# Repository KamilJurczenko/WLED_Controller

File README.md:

# WLED_Controller
My first designed pcb board to control some LEDs with a ESP-WROOM-32.

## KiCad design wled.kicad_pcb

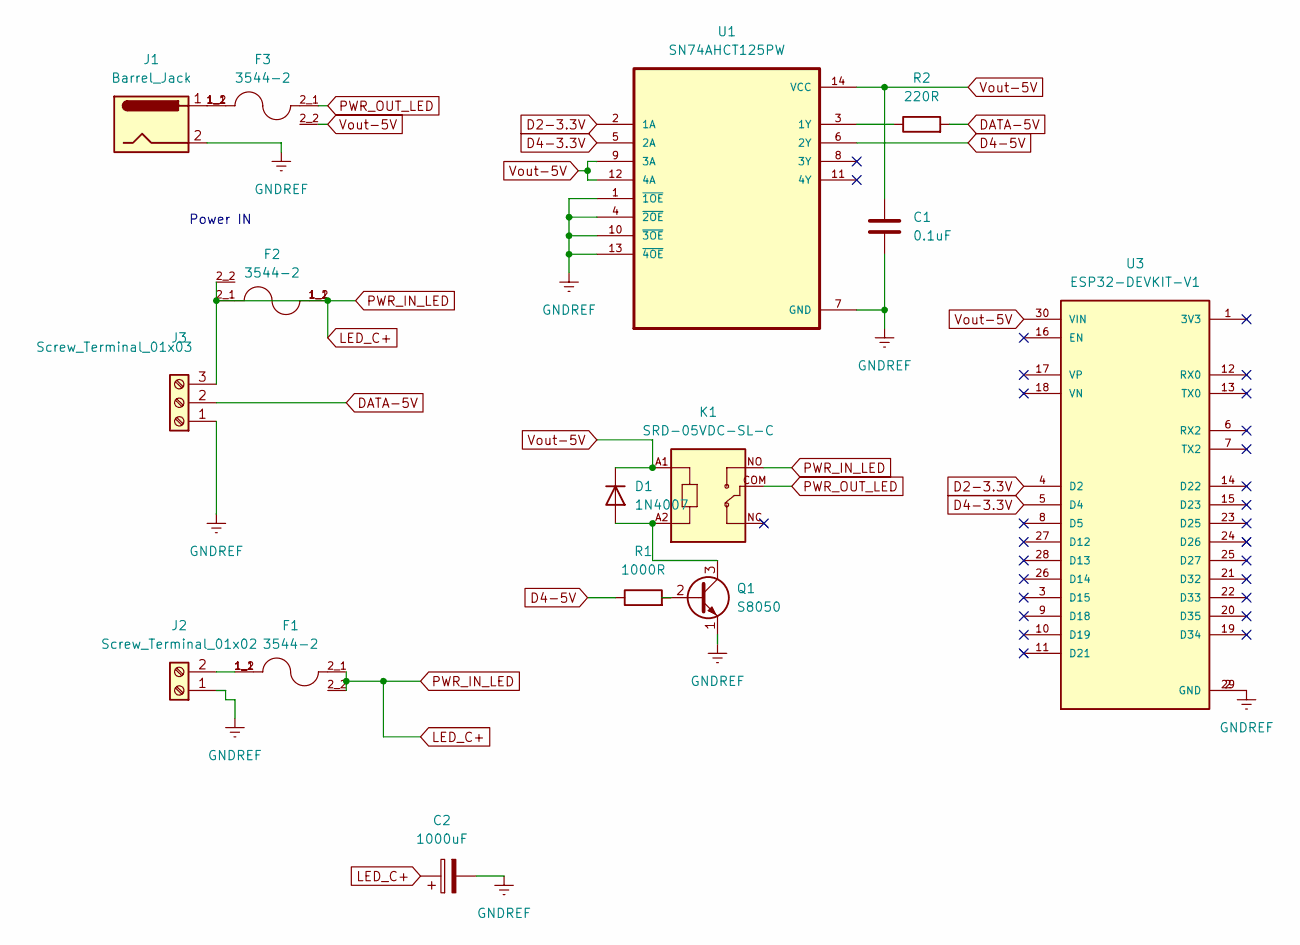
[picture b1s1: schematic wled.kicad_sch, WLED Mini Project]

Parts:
C1: 0.1uF; C_Disc_D5.0mm_W2.5mm_P2.50mm
C2: 1000uF; CP_Radial_D10.0mm_P5.00mm
D1: 1N4007; D_DO-41_SOD81_P10.16mm_Horizontal
F1, F2, F3: 3544-2; FUSE_3544-2; PARTREV C
J1: Barrel_Jack; BarrelJack_Horizontal
J2: Screw_Terminal_01x02; TerminalBlock_Phoenix_MKDS-1,5-2-5.08_1x02_P5.08mm_Horizont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
J3: Screw_Terminal_01x03; TerminalBlock_Phoenix_MKDS-1,5-3_1x03_P5.00mm_Horizontal
K1: SRD-05VDC-SL-C; RELAY_SRD-05VDC-SL-C
Q1: S8050; TO-92_Inline
R1: 1000R; R_Axial_DIN0207_L6.3mm_D2.5mm_P7.62mm_Horizontal
R2: 220R; R_Axial_DIN0207_L6.3mm_D2.5mm_P7.62mm_Horizontal
U1: SN74AHCT125PW; DIP794W45P254L1930H508Q14
U3: ESP32-DEVKIT-V1; MODULE_ESP32_DEVKIT_V1; PARTREV N/A

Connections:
D2-3.3V: U1.2 (1A), U3.4 (D2)
D4-3.3V: U1.5 (2A), U3.5 (D4)
D4-5V: R1.1, U1.6 (2Y)
DATA-5V: J3.2, R2.2
GNDREF: C1.2, C2.2, J1.2, J2.1, J3.1, Q1.1 (E), U1.1 (~1OE), U1.4 (~2OE), U1.7 (GND), U1.10 (~3OE), U1.13 (~4OE), U3.2 (GND), U3.29 (GND)
LED_C+: C2.1, F1.2_1, F1.2_2, F2.1_1, F2.1_2, F2.2_1, F2.2_2, J3.3, K1.NO
unnamed: D1.2 (A), K1.A2, Q1.3 (C)
unnamed: F3.1_1, F3.1_2, J1.1
unnamed: F1.1_1, F1.1_2, J2.2
unnamed: Q1.2 (B), R1.2
unnamed: R2.1, U1.3 (1Y)
PWR_OUT_LED: F3.2_1, K1.COM
Vout-5V: C1.1, D1.1 (K), F3.2_2, K1.A1, U1.9 (3A), U1.12 (4A), U1.14 (VCC), U3.30 (VIN)

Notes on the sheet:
Power IN

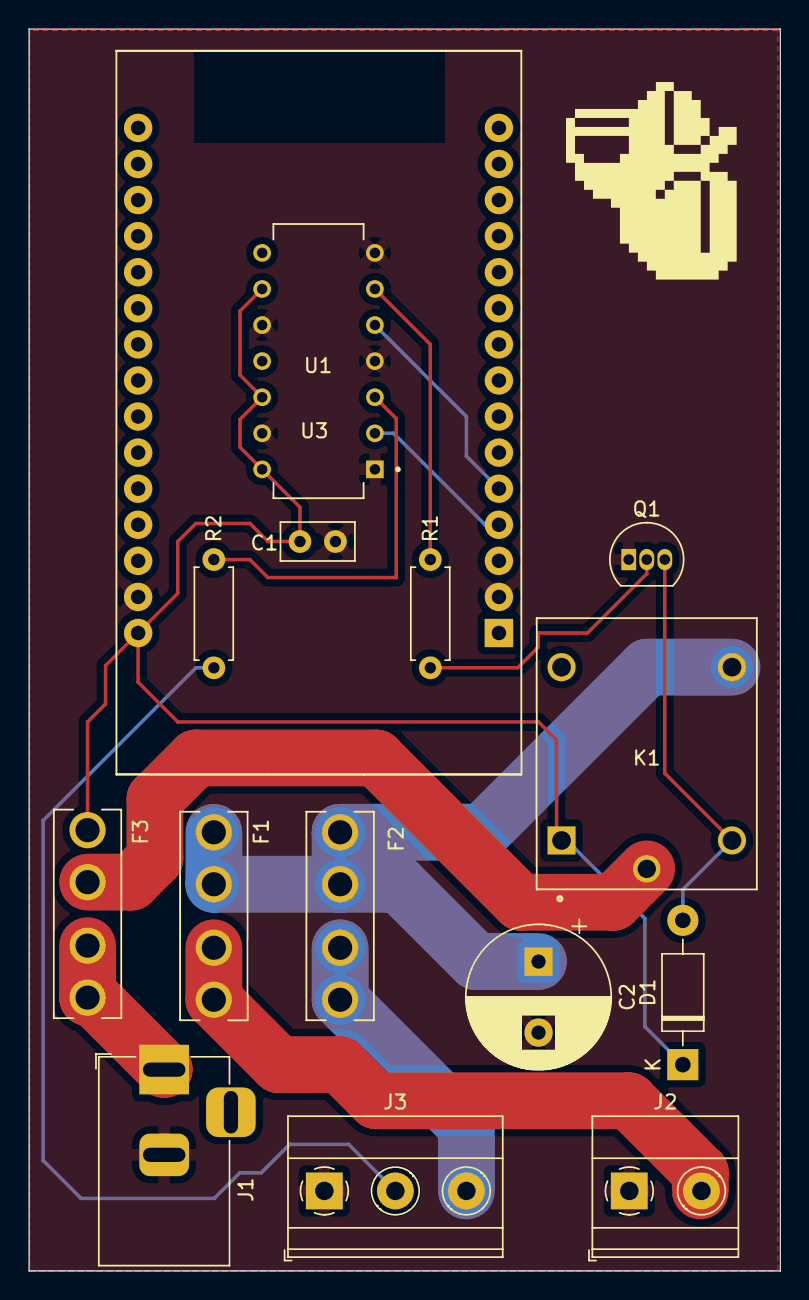
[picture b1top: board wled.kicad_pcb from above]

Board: 2 copper layers, 52.9 x 87.4 mm, 15 parts (0 on the bottom side), 13 nets.
